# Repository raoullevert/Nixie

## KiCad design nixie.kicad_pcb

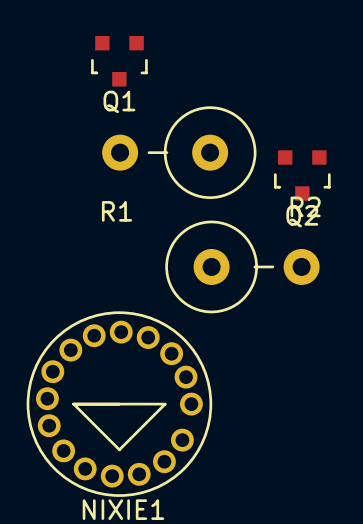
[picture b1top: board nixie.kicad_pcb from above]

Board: 2 copper layers, 5 parts (0 on the bottom side), 4 nets, no tracks yet.

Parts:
NIXIE1: CD81
Q1, Q2: MPSA42; SOT-23
R1: 390; Resistor_Vertical_RM5mm
R2: R_Small; Resistor_Vertical_RM5mm

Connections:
unnamed: NIXIE1.10, R2.1
unnamed: Q1.3, R1.2
unnamed: Q2.2, R1.1
unnamed: Q2.3, R2.2

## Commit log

2015-07-20 :tada: Added .gitattributes & .gitignore files
2015-07-20 Montages Nixies
2015-07-20 Revert "Montages Nixies"
    This reverts commit 282fb6c6172f330092db8585a2006ca15ce5ab4c.
